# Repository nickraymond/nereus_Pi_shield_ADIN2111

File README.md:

# N6 Shield ADIN2111: in development, nothing designed yet

Branch `n6-shield`, started 2026-11-17. A shield for the back of the N6 board with Sofar's Bristlemouth mote
circuit, a 5 V supply and the motor driver, as small as possible.

**Read `BRIEF.md` first.** The project in `N6_Shield_ADIN2111/` is still an unchanged copy of the Pi Zero
side-entry shield (branch `pi-zero-side-entry`); it is the starting point, not an N6 design. Do not build it.

Docs, tools, references and the history of the Pi shields are on the `development` branch (`START_HERE.md`).

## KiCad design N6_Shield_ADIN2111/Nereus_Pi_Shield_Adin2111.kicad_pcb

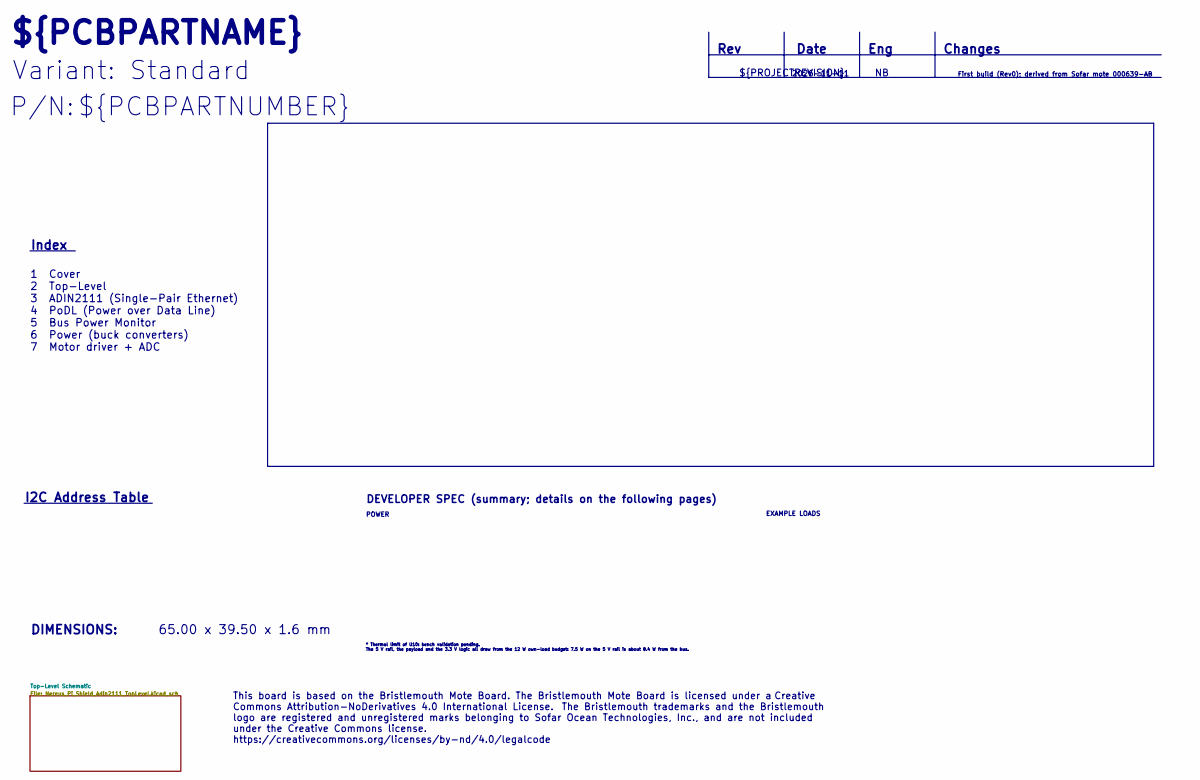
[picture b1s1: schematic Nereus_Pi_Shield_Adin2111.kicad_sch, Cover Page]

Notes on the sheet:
Variant: Standard
Date
${PCBPARTNAME}
Changes
${PCBPARTNUMBER}
First build (Rev0); derived from Sofar mote 000639-AB
Index
DEVELOPER SPEC (summary; details on the following pages)
2026-11-11
${PROJECTREVISION}
Rev
I2C Address Table
POWER
Eng
65.00 x 39.50 x 1.6 mm
1 Cover 2 Top-Level 3 ADIN2111 (Single-Pair Ethernet) 4 PoDL (Power over Data Line) 5 Bus Power Monitor 6 Power (buck converters) 7 Motor driver + ADC
* Thermal limit of U10: bench validation pending. The 5 V rail, the payload and the 3.3 V logic all draw from the 12 W own-load budget: 7.5 W on the 5 V rail is about 8.4 W from the bus.
P/N:
DIMENSIONS:
EXAMPLE LOADS
This board is based on the Bristlemouth Mote Board. The Bristlemouth Mote Board is licensed under a Creative Commons Attribution-NoDerivatives 4.0 International License. The Bristlemouth trademarks and the Bristlemouth logo are registered and unregistered marks belonging to Sofar Ocean Technologies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

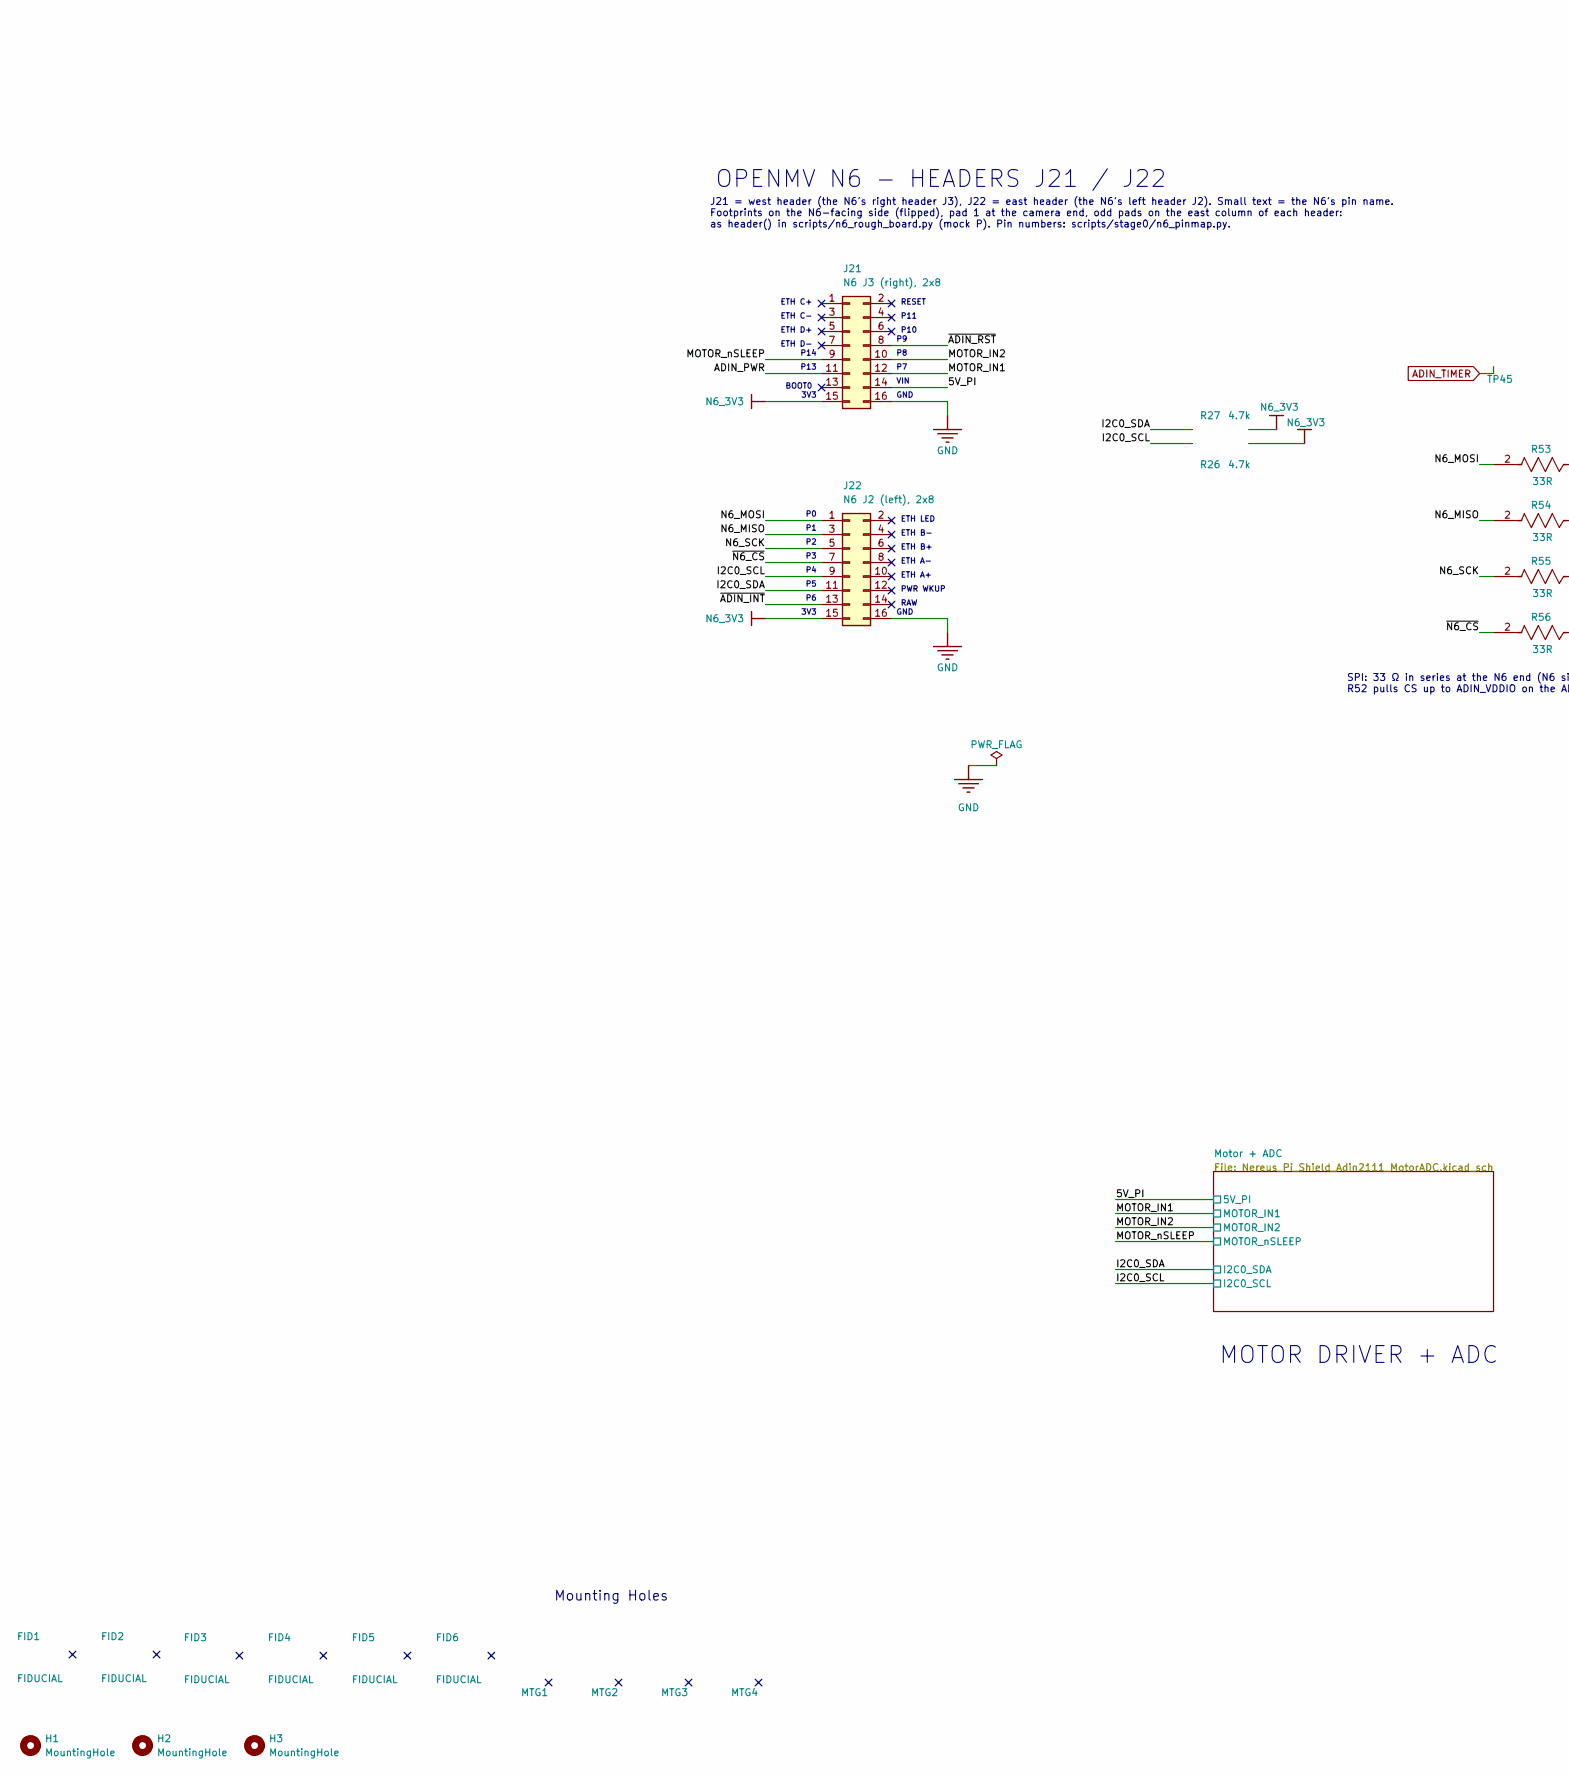
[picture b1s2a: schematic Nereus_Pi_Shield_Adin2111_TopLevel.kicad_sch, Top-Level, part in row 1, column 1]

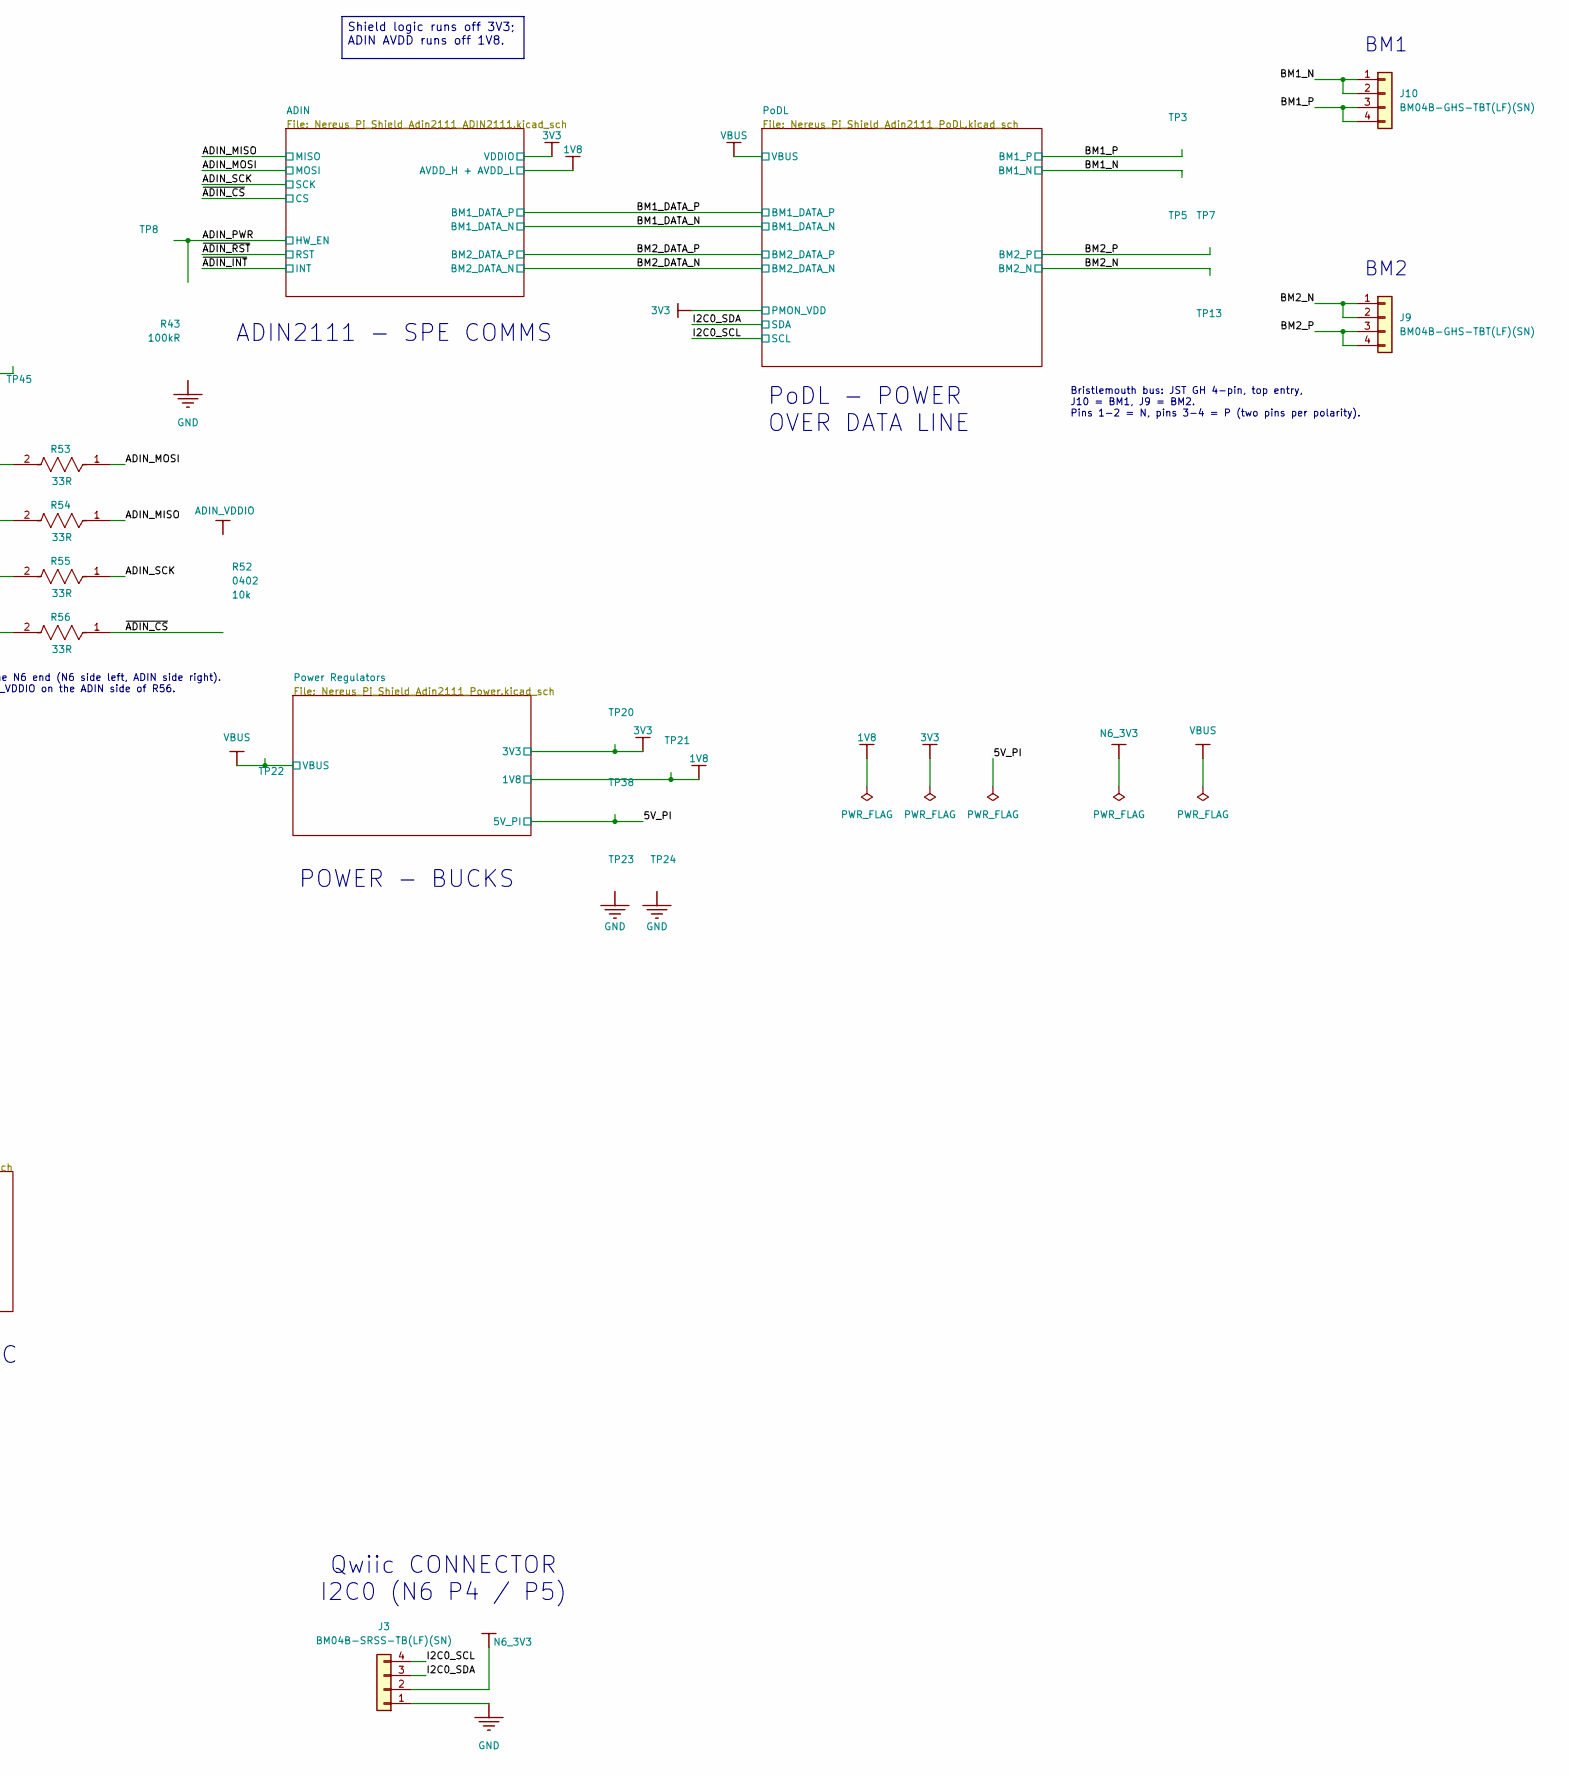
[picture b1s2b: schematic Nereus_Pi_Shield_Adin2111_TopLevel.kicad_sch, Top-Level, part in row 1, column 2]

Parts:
FID1, FID2, FID3, FID4, FID5, FID6: FIDUCIAL; FIDUCIAL_075MM
H1, H2, H3: MountingHole; MountingHole_2.7mm_M2.5_ISO7380
J3: BM04B-SRSS-TB(LF)(SN); JST_SH_BM04B-SRSS-TB_1x04-1MP_P1.00mm_Vertical
J9, J10: BM04B-GHS-TBT(LF)(SN); JST_GH_BM04B-GHS-TBT_1x04-1MP_P1.25mm_Vertical
J21: N6 J3 (right), 2x8; PinHeader_2x08_P2.54mm_Vertical
J22: N6 J2 (left), 2x8; PinHeader_2x08_P2.54mm_Vertical
MTG1, MTG2, MTG3, MTG4: Hole_M3
R26, R27: ERJ-2RKF4701X; RESC1005X40X25LL05T05; TOLERANCE 1%; VOLTAGE RATING 50 V; PARTNUMBER ERJ-2RKF4701X
R43: RMCF0402FT100K; FP-RMCF0402-IPC_C; TOLERANCE 1%; POWER RATING 62.5mW
R52: RC0402JR-0710KL; FP-RC0402-0_4-IPC_C; RESISTANCE TOLERANCE 5%; POWER RATING 62.5mW
R53, R54, R55, R56: 0402WGF330JTCE; FP-RC0402-0_4-IPC_B; WORKING VOLTAGE 50V; RESISTANCE TOLERANCE 1%
TP3, TP5, TP7, TP8, TP13, TP20, TP21, TP22, TP23, TP24, TP38, TP45: TEST_POINT; PCB_TP_1.5mm; PARTTYPE non BOM

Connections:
1V8: TP21.1 (1_1); also elsewhere on the board
3V3: TP20.1 (1_1); also elsewhere on the board
/Top-Level Schematic/5V_PI: J21.14, TP38.1 (1_1); also elsewhere on the board
/Top-Level Schematic/ADIN_MISO: R54.1; also elsewhere on the board
/Top-Level Schematic/ADIN_MOSI: R53.1; also elsewhere on the board
/Top-Level Schematic/ADIN_PWR: J21.11, R43.1, TP8.1 (1_1); also elsewhere on the board
/Top-Level Schematic/ADIN_SCK: R55.1; also elsewhere on the board
/Top-Level Schematic/BM1_N: J10.1, J10.2, TP5.1 (1_1); also elsewhere on the board
/Top-Level Schematic/BM1_P: J10.3, J10.4, TP3.1 (1_1); also elsewhere on the board
/Top-Level Schematic/BM2_N: J9.1, J9.2, TP13.1 (1_1); also elsewhere on the board
/Top-Level Schematic/BM2_P: J9.3, J9.4, TP7.1 (1_1); also elsewhere on the board
/Top-Level Schematic/I2C0_SCL: J3.4, J22.9, R26.1; also elsewhere on the board
/Top-Level Schematic/I2C0_SDA: J3.3, J22.11, R27.1; also elsewhere on the board
/Top-Level Schematic/MOTOR_IN1: J21.12; also elsewhere on the board
/Top-Level Schematic/MOTOR_IN2: J21.10; also elsewhere on the board
/Top-Level Schematic/MOTOR_nSLEEP: J21.9; also elsewhere on the board
/Top-Level Schematic/N6_MISO: J22.3, R54.2
/Top-Level Schematic/N6_MOSI: J22.1, R53.2
/Top-Level Schematic/N6_SCK: J22.5, R55.2
/Top-Level Schematic/~ADIN_CS: R52.2, R56.1; also elsewhere on the board
/Top-Level Schematic/~ADIN_INT: J22.13; also elsewhere on the board
/Top-Level Schematic/~ADIN_RST: J21.8; also elsewhere on the board
/Top-Level Schematic/~N6_CS: J22.7, R56.2
ADIN_TIMER: TP45.1 (1_1); also elsewhere on the board
ADIN_VDDIO: R52.1; also elsewhere on the board
GND: J3.1, J21.16, J22.16, R43.2, TP23.1 (1_1), TP24.1 (1_1); also elsewhere on the board
N6_3V3: J3.2, J21.15, J22.15, R26.2, R27.2; also elsewhere on the board
VBUS: TP22.1 (1_1); also elsewhere on the board

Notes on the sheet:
ETH C-
RAW
J21 = west header (the N6's right header J3), J22 = east header (the N6's left header J2). Small text = the N6's pin name. Footprints on the N6-facing side (flipped), pad 1 at the camera end, odd pads on the east column of each header: as header() in scripts/n6_rough_board.py (mock P). Pin numbers: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
P11
GND
RESET
ETH LED
ETH B+
3V3
P13
BM1
PWR WKUP
VIN
ETH B-
BM2
Bristlemouth bus: JST GH 4-pin, top entry, J10 = BM1, J9 = BM2. Pins 1-2 = N, pins 3-4 = P (two pins per polarity).
ETH D-
ETH D+
P14
BOOT0
ETH C+
SPI: 33 Ω in series at the N6 end (N6 side left, ADIN side right). R52 pulls CS up to ADIN_VDDIO on the ADIN side of R56.
ETH A+
ETH A-
P10
Shield logic runs off 3V3; ADIN AVDD runs off 1V8.
MOTOR DRIVER + ADC
Qwiic CONNECTOR I2C0 (N6 P4 / P5)
OPENMV N6 - HEADERS J21 / J22
PoDL - POWER OVER DATA LINE
ADIN2111 - SPE COMMS
Mounting Holes
POWER - BUCKS

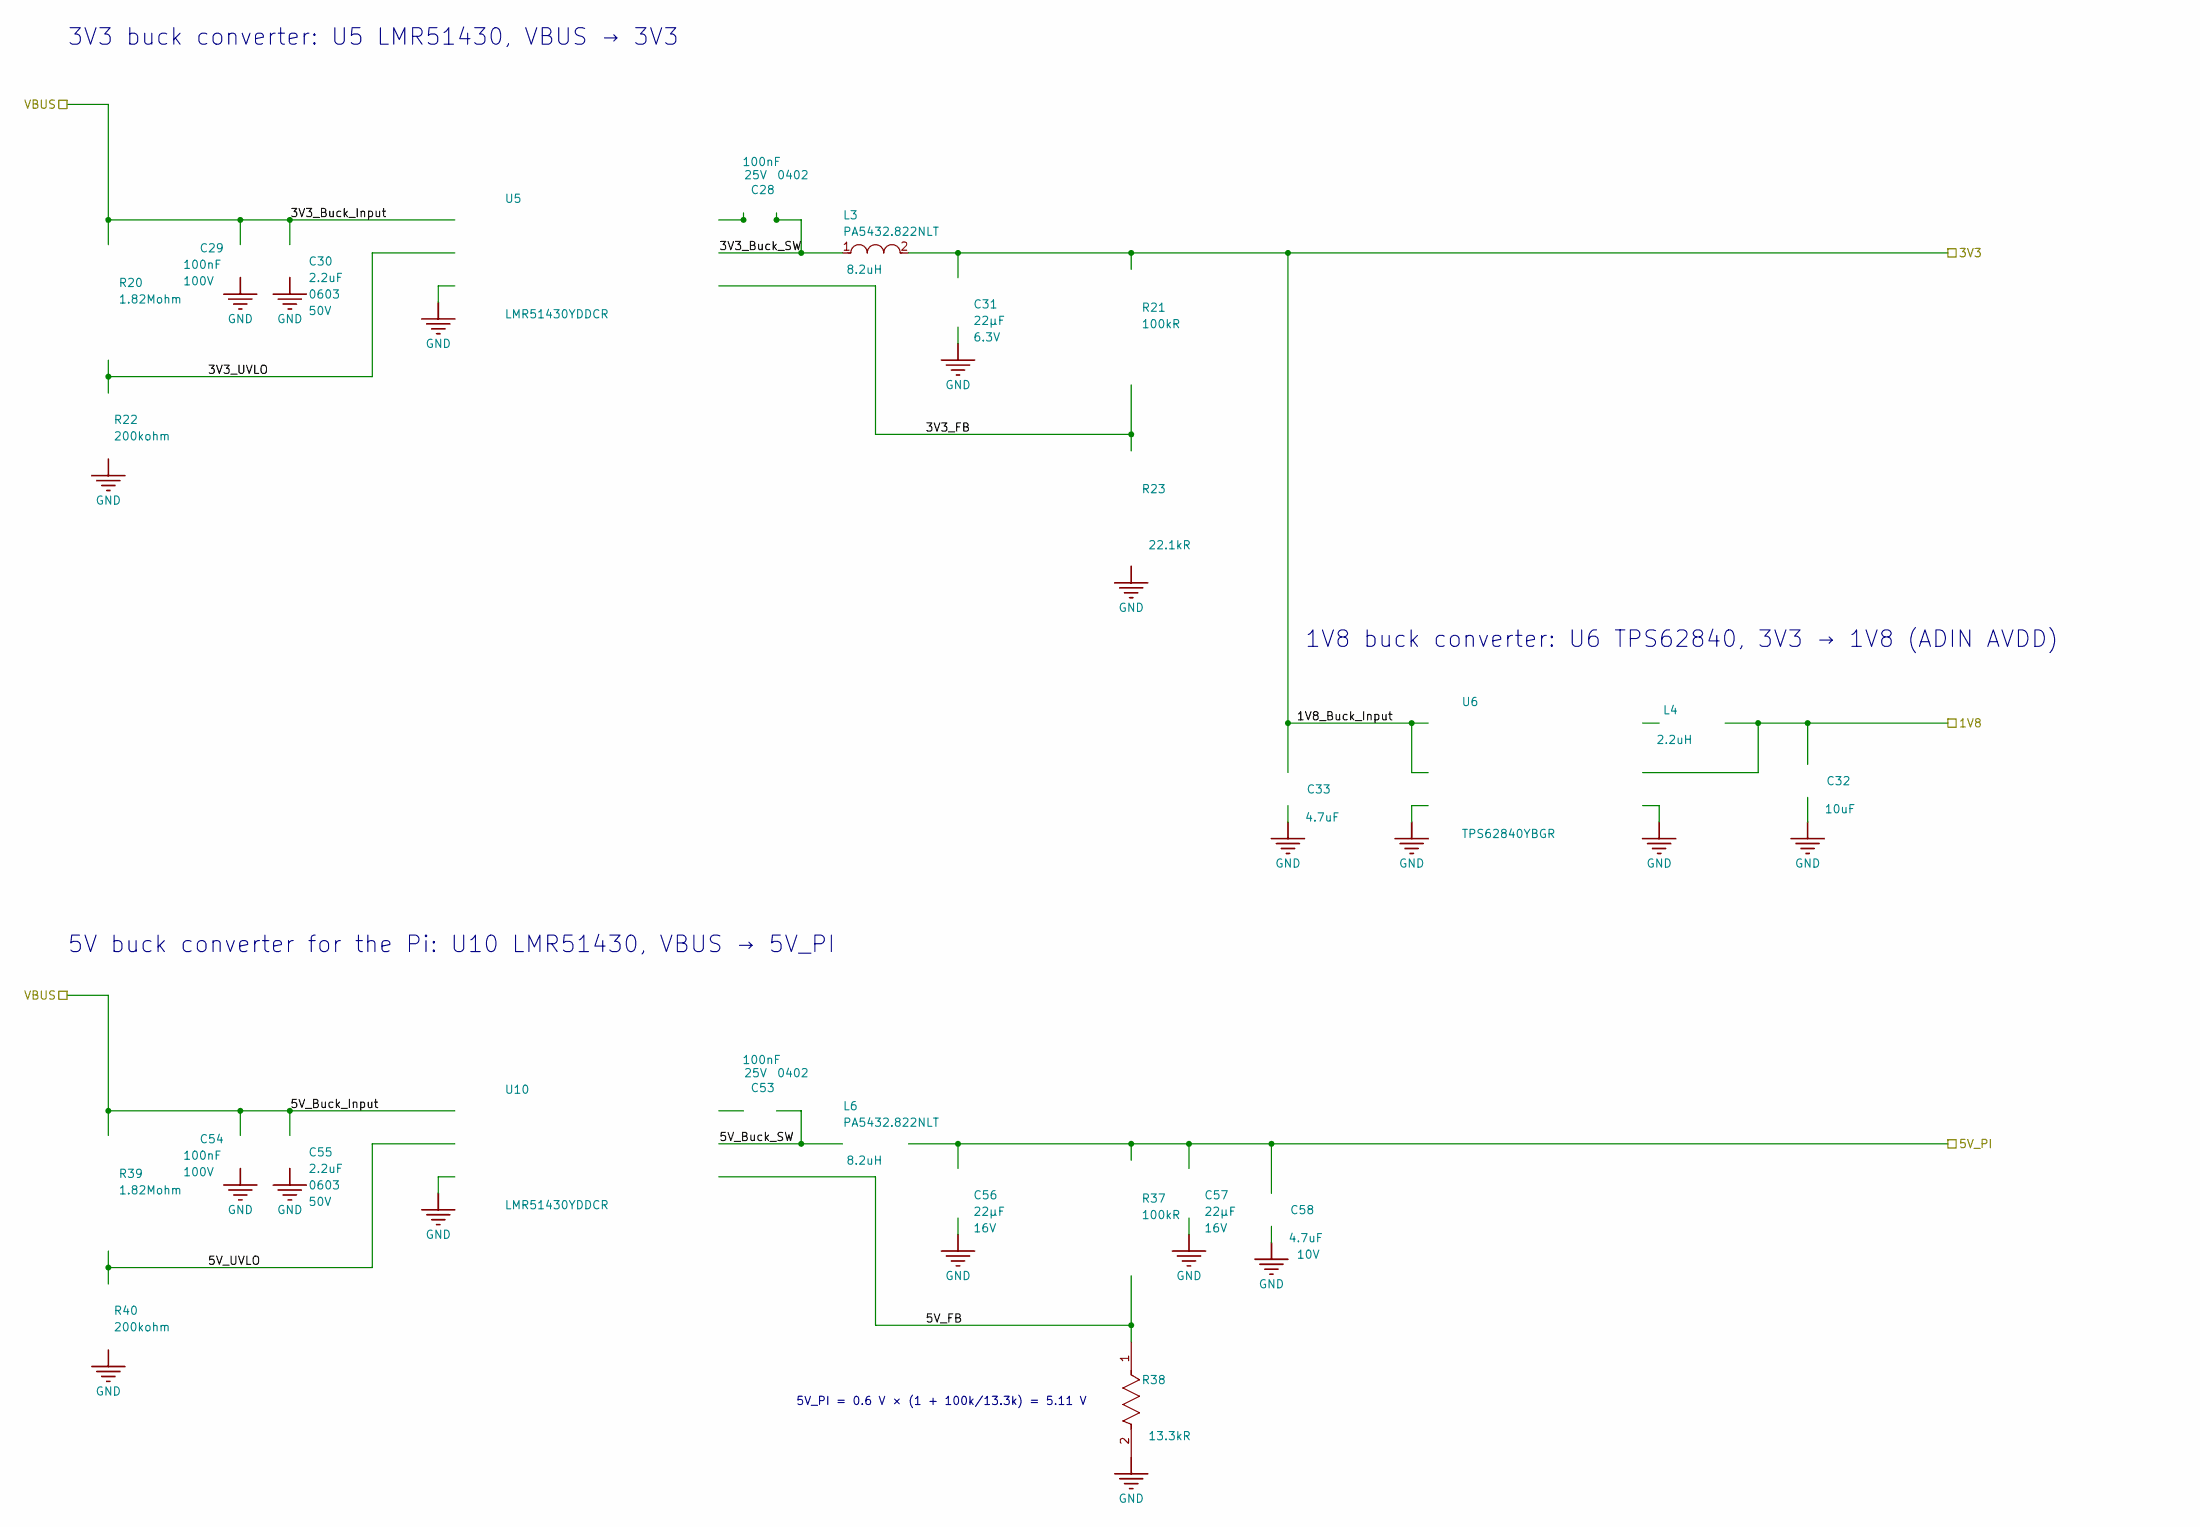
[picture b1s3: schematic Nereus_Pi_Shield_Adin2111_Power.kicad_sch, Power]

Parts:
C28, C53: CL05A104KA5NNNC; FP-CL278-IPC_C; VOLTAGE 25V; VOLTAGE RATING 25V
C29, C54: GRM188R72A104KA35D; FP-GRM188-0_1-e0_2_0_5-IPC_B; VOLTAGE RATING (DC) 100V; VOLTAGE 100V
C30, C55: UMK107BBJ225KA-T; FP-0603-L_1_6_0_2-W_0_8_0-MFG; VOLTAGE RATING 50V; TOLERANCE 10%
C31: C1608X5R0J226M080AC; CAPC1608X100X20ML10; TOLERANCE ±20%; VOLTAGE - RATED 6.3V
C32: GRJ155R60J106ME11D; FP-GRJ155-0_2-MFG; TOLERANCE 20%; VOLTAGE RATING 6.3V
C33: GRM155R60J475ME87D; FP-GRM155-0_15-MFG; TOLERANCE 20%; VOLTAGE 6.3V
C56, C57: GRM21BR61C226ME44L; C_0805_2012Metric; TOLERANCE ±20%; VOLTAGE - RATED 16V
C58: GRM155R61A475MEAAD; C_0402_1005Metric; TOLERANCE 20%; VOLTAGE RATING 10V
L3, L6: PA5432.822NLT; FP-PA5432_472NLT-MFG
L4: DFE201612E-2R2M=P2; FP-DFE201612C-MFG
R20, R39: CRCW04021M82FKED; FP-CRCW0402-e3-MFG; RESISTANCE TOLERANCE 1%; POWER RATING 63mW
R21, R37: RMCF0402FT100K; FP-RMCF0402-IPC_C; TOLERANCE 1%; POWER RATING 62.5mW
R22, R40: RC0402FR-07200KL; RESC1005X40X25LL05T10; PART NUMBER RC0402FR-07200KL
R23: RC0402FR-0722K1L; FP-RC0402-0_4-IPC_B; WORKING VOLTAGE 50V; RESISTANCE TOLERANCE 1%
R38: 0402WGF1332TCE; FP-RC0402-0_4-IPC_B; WORKING VOLTAGE 50V; RESISTANCE TOLERANCE 1%
U5, U10: LMR51430YDDCR; SOT-23-THIN-6_DDC_TEX; MANUFACTURER_PART_NUMBER LMR51430YDDCR
U6: TPS62840YBGR; FP-YBG0006-MFG

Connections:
1V8: C32.1, L4.2, U6.A2 (VOS); also elsewhere on the board
3V3: C31.2, C33.1, L3.2, R21.1, U6.B1 (VIN), U6.C1 (EN); also elsewhere on the board
/Top-Level Schematic/5V_PI: C56.2, C57.2, C58.1, L6.2, R37.1; also elsewhere on the board
/Top-Level Schematic/Power Regulators/3V3_Buck_SW: C28.1, L3.1, U5.2 (SW)
/Top-Level Schematic/Power Regulators/3V3_FB: R21.2, R23.1, U5.4 (FB)
/Top-Level Schematic/Power Regulators/3V3_UVLO: R20.1, R22.2, U5.5 (EN)
/Top-Level Schematic/Power Regulators/5V_Buck_SW: C53.1, L6.1, U10.2 (SW)
/Top-Level Schematic/Power Regulators/5V_FB: R37.2, R38.1, U10.4 (FB)
/Top-Level Schematic/Power Regulators/5V_UVLO: R39.1, R40.2, U10.5 (EN)
GND: C29.2, C30.2, C31.1, C32.2, C33.2, C54.2, C55.2, C56.1, C57.1, C58.2, R22.1, R23.2, R38.2, R40.1, U5.1 (GND), U6.A1 (GND), U6.C2 (VSET), U10.1 (GND); also elsewhere on the board
unnamed: C28.2, U5.6 (CB)
unnamed: L4.1, U6.B2 (SW)
unnamed: C53.2, U10.6 (CB)
VBUS: C29.1, C30.1, C54.1, C55.1, R20.2, R39.2, U5.3 (VIN), U10.3 (VIN); also elsewhere on the board

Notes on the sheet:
1V8 buck converter: U6 TPS62840, 3V3 → 1V8 (ADIN AVDD)
3V3 buck converter: U5 LMR51430, VBUS → 3V3
5V buck converter for the Pi: U10 LMR51430, VBUS → 5V_PI
5V_PI = 0.6 V × (1 + 100k/13.3k) = 5.11 V

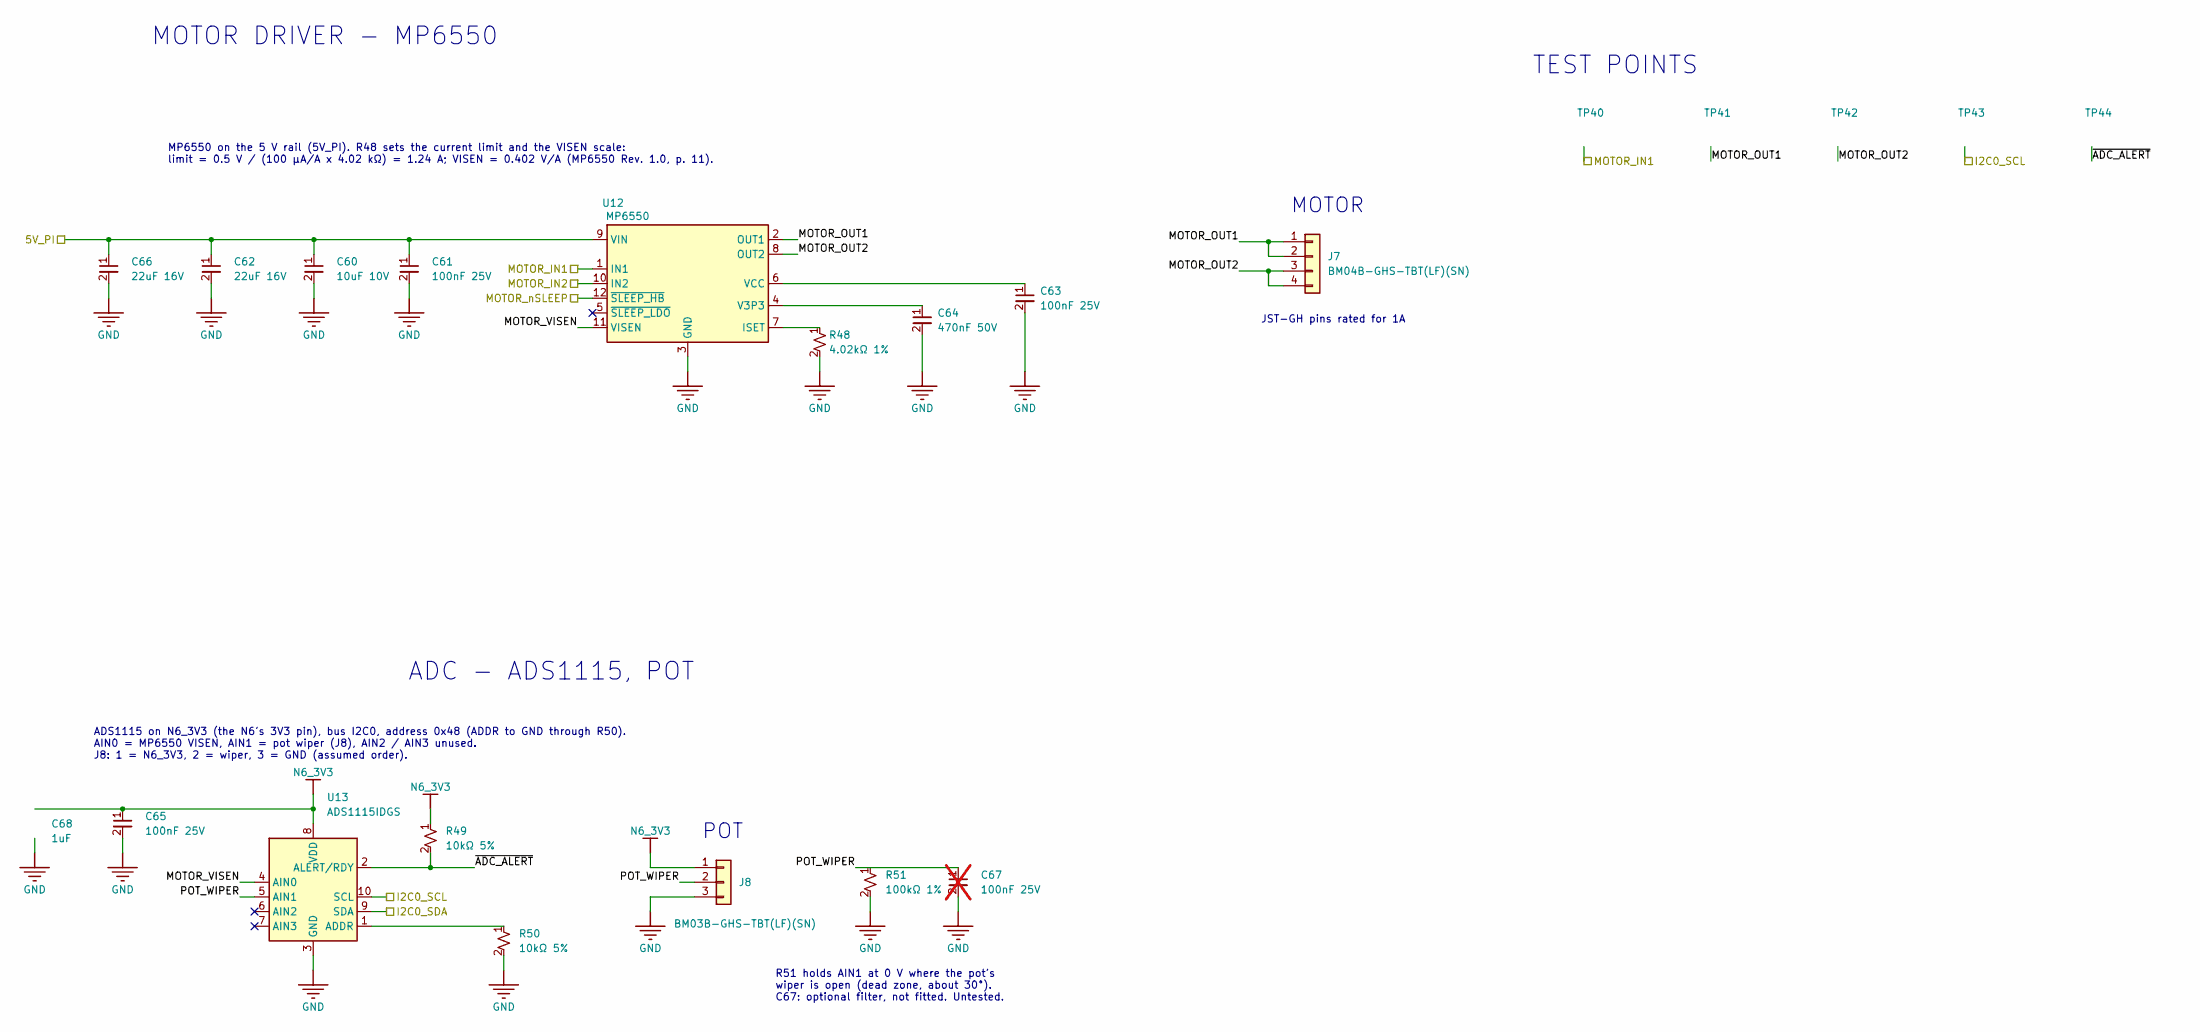
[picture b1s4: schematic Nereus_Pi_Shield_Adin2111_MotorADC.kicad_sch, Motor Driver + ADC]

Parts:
C60: 10uF 10V; C_0402_1005Metric_Pad0.74x0.62mm_HandSolder
C61, C63, C65: 100nF 25V; FP-CL278-IPC_C
C62, C66: 22uF 16V; C_0805_2012Metric
C64: 470nF 50V; C_0402_1005Metric_Pad0.74x0.62mm_HandSolder
C67: 100nF 25V; FP-CL278-IPC_C; not fitted
C68: CL05A105KP5NNNC; FP-CL511-IPC_C; TOLERANCE 10%; VOLTAGE RATING 10V
J7: BM04B-GHS-TBT(LF)(SN); JST_GH_BM04B-GHS-TBT_1x04-1MP_P1.25mm_Vertical
J8: BM03B-GHS-TBT(LF)(SN); JST_GH_BM03B-GHS-TBT_1x03-1MP_P1.25mm_Vertical
R48: 4.02kΩ 1%; FP-RC0402-0_4-IPC_C
R49, R50: 10kΩ 5%; FP-RC0402-0_4-IPC_C
R51: 100kΩ 1%; FP-RMCF0402-IPC_C
TP40, TP41, TP42, TP43, TP44: TEST_POINT; PCB_TP_1.5mm; PARTTYPE non BOM
U12: MP6550; MP6550GG
U13: ADS1115IDGS; TSSOP-10_3x3mm_P0.5mm

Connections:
/Top-Level Schematic/5V_PI: C60.1, C61.1, C62.1, C66.1, U12.9 (VIN); also elsewhere on the board
/Top-Level Schematic/I2C0_SCL: TP43.1 (1_1), U13.10 (SCL); also elsewhere on the board
/Top-Level Schematic/I2C0_SDA: U13.9 (SDA); also elsewhere on the board
/Top-Level Schematic/MOTOR_IN1: TP40.1 (1_1), U12.1 (IN1); also elsewhere on the board
/Top-Level Schematic/MOTOR_IN2: U12.10 (IN2); also elsewhere on the board
/Top-Level Schematic/MOTOR_nSLEEP: U12.12 (~SLEEP_HB); also elsewhere on the board
/Top-Level Schematic/Motor + ADC/MOTOR_OUT1: J7.1, J7.2, TP41.1 (1_1), U12.2 (OUT1)
/Top-Level Schematic/Motor + ADC/MOTOR_OUT2: J7.3, J7.4, TP42.1 (1_1), U12.8 (OUT2)
/Top-Level Schematic/Motor + ADC/MOTOR_VISEN: U12.11 (VISEN), U13.4 (AIN0)
/Top-Level Schematic/Motor + ADC/POT_WIPER: C67.1, J8.2, R51.1, U13.5 (AIN1)
/Top-Level Schematic/Motor + ADC/~ADC_ALERT: R49.2, TP44.1 (1_1), U13.2 (ALERT/RDY)
GND: C60.2, C61.2, C62.2, C63.2, C64.2, C65.2, C66.2, C67.2, C68.2, J8.3, R48.2, R50.2, R51.2, U12.3 (GND), U13.3 (GND); also elsewhere on the board
N6_3V3: C65.1, C68.1, J8.1, R49.1, U13.8 (VDD); also elsewhere on the board
unnamed: R48.1, U12.7 (ISET)
unnamed: C64.1, U12.4 (V3P3)
unnamed: C63.1, U12.6 (VCC)
unnamed: R50.1, U13.1 (ADDR)

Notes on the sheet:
MP6550 on the 5 V rail (5V_PI). R48 sets the current limit and the VISEN scale: limit = 0.5 V / (100 µA/A x 4.02 kΩ) = 1.24 A; VISEN = 0.402 V/A (MP6550 Rev. 1.0, p. 11).
ADS1115 on N6_3V3 (the N6's 3V3 pin), bus I2C0, address 0x48 (ADDR to GND through R50). AIN0 = MP6550 VISEN, AIN1 = pot wiper (J8), AIN2 / AIN3 unused. J8: 1 = N6_3V3, 2 = wiper, 3 = GND (assumed order).
JST-GH pins rated for 1A
POT
MOTOR
R51 holds AIN1 at 0 V where the pot's wiper is open (dead zone, about 30°). C67: optional filter, not fitted. Untested.
ADC - ADS1115, POT
MOTOR DRIVER - MP6550
TEST POINTS

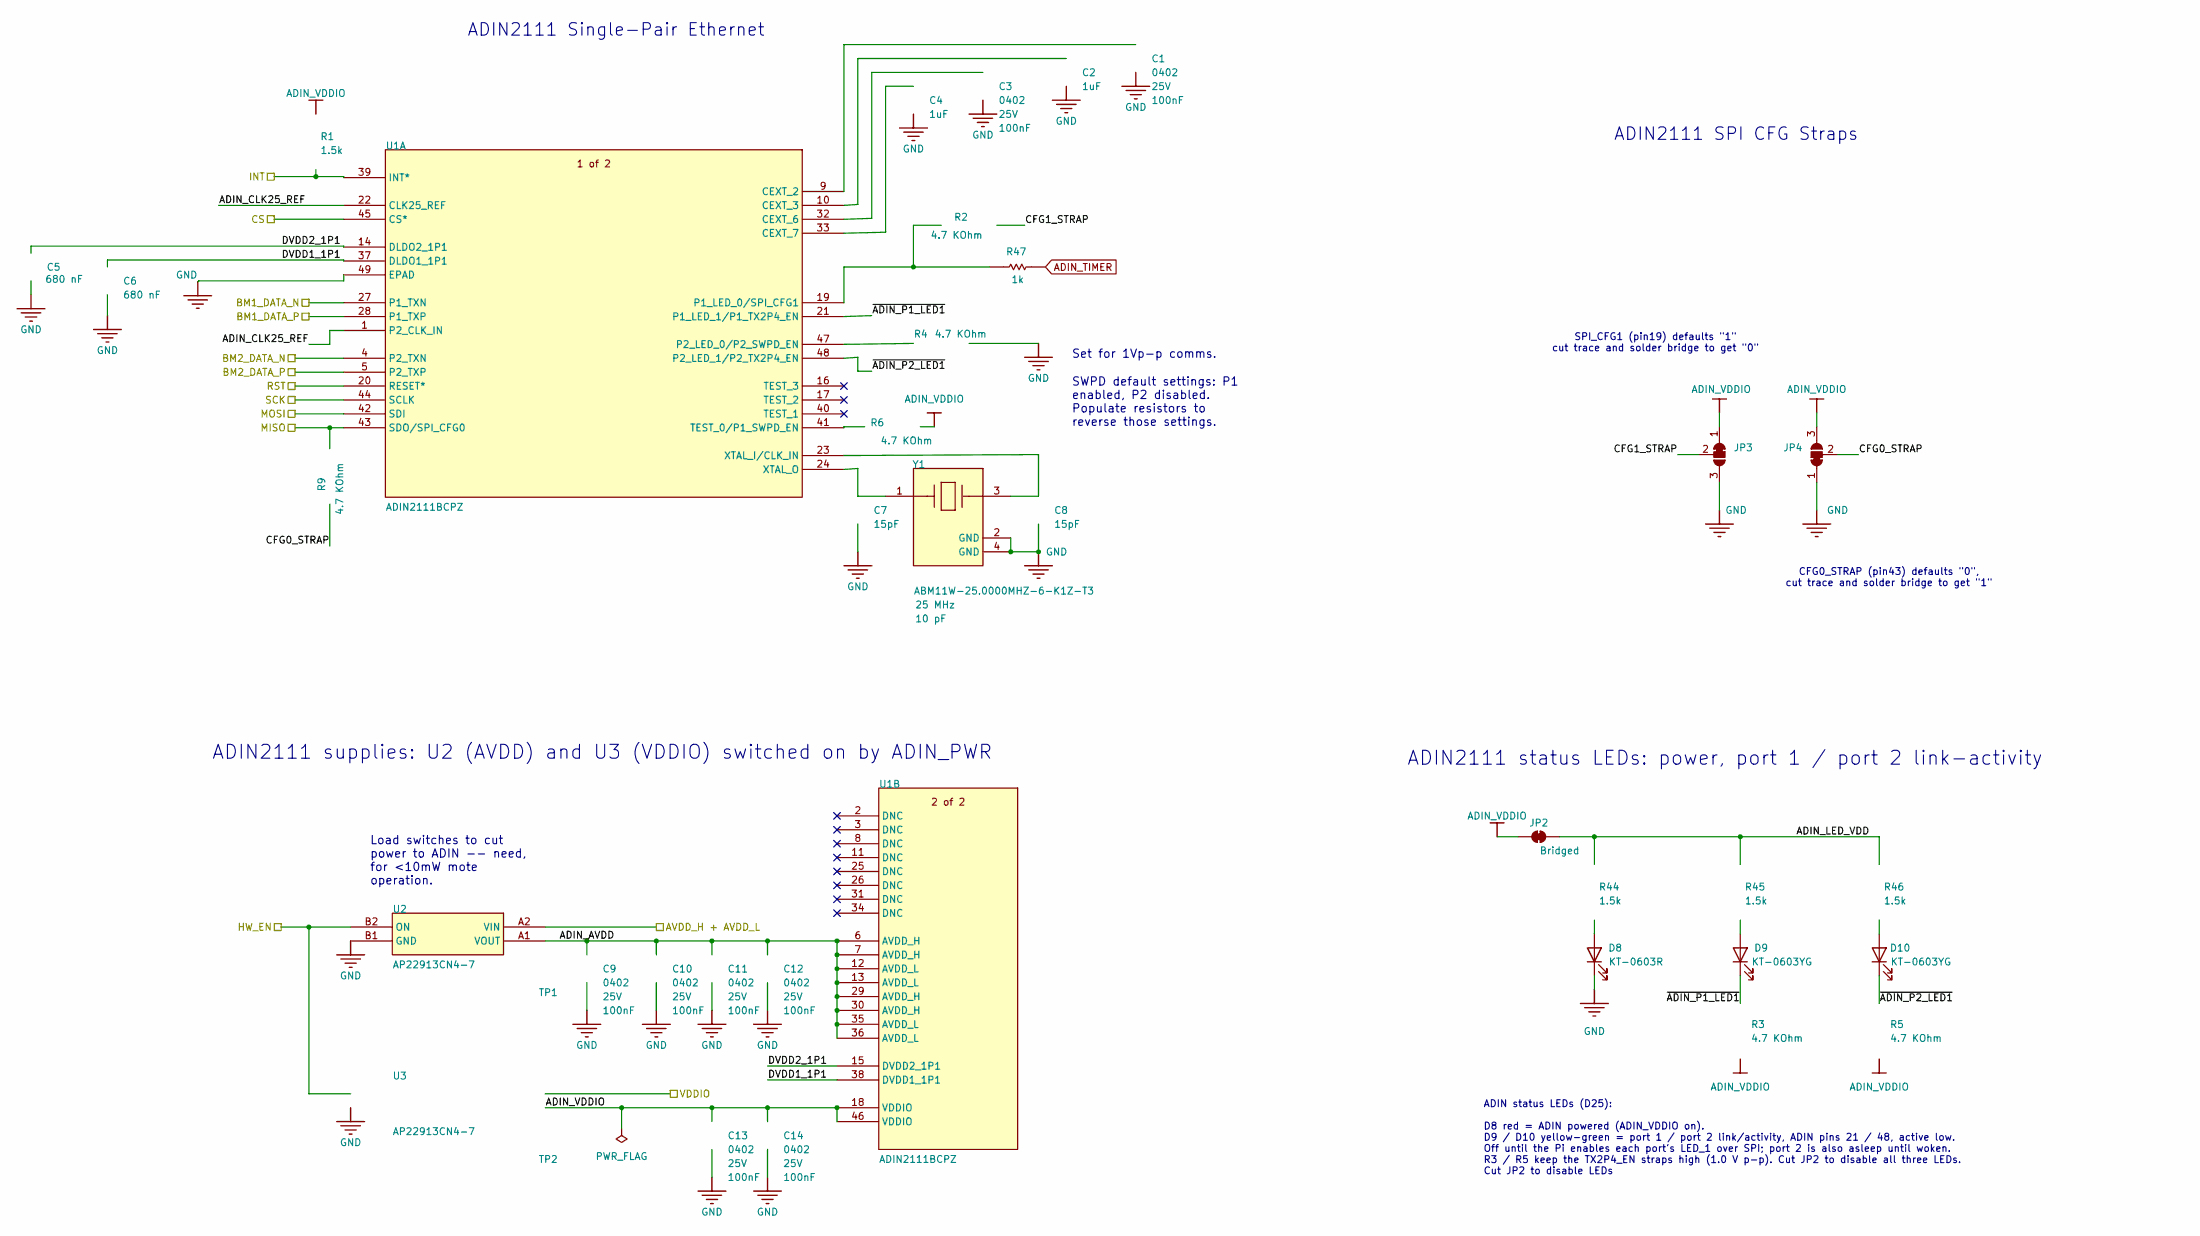
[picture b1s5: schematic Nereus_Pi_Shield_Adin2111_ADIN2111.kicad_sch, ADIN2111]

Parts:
C1, C3, C9, C10, C11, C12, C13, C14: CL05A104KA5NNNC; FP-CL278-IPC_C; VOLTAGE 25V; VOLTAGE RATING 25V
C2, C4: CL05A105KP5NNNC; FP-CL511-IPC_C; TOLERANCE 10%; VOLTAGE RATING 10V
C5, C6: CC0402KRX5R6BB684; FP-CC0402-MFG; TOLERANCE 0.1; VOLTAGE RATING 10 V; MANUFACTURER PART NUMBER CC0402KRX5R6BB684; DIGIKEY DESCRIPTION CAP CER 0.68UF 10V X5R 0402
C7, C8: CC0402JRNPO9BN150; FP-CC0402-0_55-IPC_B; VOLTAGE RATING (DC) 50V; VOLTAGE RATING 50V
D8: KT-0603R; LED_0603_1608Metric; LCSC C2286
D9, D10: KT-0603YG; LED_0603_1608Metric; LCSC C2289
JP2: Bridged; SolderJumper-2_R1210_Bridged_NetTie
JP3, JP4: SolderJumper_3_Bridged12; SolderJumper-3_P1.3mm_Bridged12_RoundedPad1.0x1.5mm
R1, R44, R45, R46: RC0402FR-071K5L; RESC1005X40X25ML05T10; PART NUMBER RC0402FR-071K5L
R2, R3, R4, R5, R6, R9: ERJ-2RKF4701X; RESC1005X40X25LL05T05; TOLERANCE 1%; VOLTAGE RATING 50 V; PARTNUMBER ERJ-2RKF4701X
R47: RC0402FR-071KL; RESC1005X40X25ML05T10; PART NUMBER RC0402FR-071KL
TP1, TP2: TEST_POINT; PCB_TP_1.5mm; PARTTYPE non BOM
U1: ADIN2111BCPZ; ADIN2111BCPZ-Footprint-1
U2, U3: AP22913CN4-7; AP22913CN4-7-Footprint-1
Y1: ABM11W-25.0000MHZ-6-K1Z-T3; FP-ABM11W-MFG

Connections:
1V8: U2.A2 (VIN); also elsewhere on the board
3V3: U3.A2 (VIN); also elsewhere on the board
/Top-Level Schematic/ADIN/ADIN_AVDD: C9.1, C10.1, C11.1, C12.1, TP1.1 (1_1), U1.6 (AVDD_H), U1.7 (AVDD_H), U1.12 (AVDD_L), U1.13 (AVDD_L), U1.29 (AVDD_H), U1.30 (AVDD_H), U1.35 (AVDD_L), U1.36 (AVDD_L), U2.A1 (VOUT)
/Top-Level Schematic/ADIN/ADIN_CLK25_REF: U1.1 (P2_CLK_IN), U1.22 (CLK25_REF)
/Top-Level Schematic/ADIN/ADIN_LED_VDD: JP2.2 (B), R44.2, R45.2, R46.2
/Top-Level Schematic/ADIN/CFG0_STRAP: JP4.2 (C), R9.1
/Top-Level Schematic/ADIN/CFG1_STRAP: JP3.2 (C), R2.2
/Top-Level Schematic/ADIN/DVDD1_1P1: C6.1, U1.37 (DLDO1_1P1), U1.38 (DVDD1_1P1)
/Top-Level Schematic/ADIN/DVDD2_1P1: C5.1, U1.14 (DLDO2_1P1), U1.15 (DVDD2_1P1)
/Top-Level Schematic/ADIN/~ADIN_P1_LED1: D9.1 (K), R3.1, U1.21 (P1_LED_1/P1_TX2P4_EN)
/Top-Level Schematic/ADIN/~ADIN_P2_LED1: D10.1 (K), R5.1, U1.48 (P2_LED_1/P2_TX2P4_EN)
/Top-Level Schematic/ADIN_MISO: R9.2, U1.43 (SDO/SPI_CFG0); also elsewhere on the board
/Top-Level Schematic/ADIN_MOSI: U1.42 (SDI); also elsewhere on the board
/Top-Level Schematic/ADIN_PWR: U2.B2 (ON), U3.B2 (ON); also elsewhere on the board
/Top-Level Schematic/ADIN_SCK: U1.44 (SCLK); also elsewhere on the board
/Top-Level Schematic/BM1_DATA_N: U1.27 (P1_TXN); also elsewhere on the board
/Top-Level Schematic/BM1_DATA_P: U1.28 (P1_TXP); also elsewhere on the board
/Top-Level Schematic/BM2_DATA_N: U1.4 (P2_TXN); also elsewhere on the board
/Top-Level Schematic/BM2_DATA_P: U1.5 (P2_TXP); also elsewhere on the board
/Top-Level Schematic/~ADIN_CS: U1.45 (CS*); also elsewhere on the board
/Top-Level Schematic/~ADIN_INT: R1.1, U1.39 (INT*); also elsewhere on the board
/Top-Level Schematic/~ADIN_RST: U1.20 (RESET*); also elsewhere on the board
ADIN_TIMER: R47.1; also elsewhere on the board
ADIN_VDDIO: C13.1, C14.1, JP2.1 (A), JP3.1 (A), JP4.3 (B), R1.2, R3.2, R5.2, R6.2, TP2.1 (1_1), U1.18 (VDDIO), U1.46 (VDDIO), U3.A1 (VOUT); also elsewhere on the board
GND: C1.2, C2.2, C3.2, C4.2, C5.2, C6.2, C7.2, C8.2, C9.2, C10.2, C11.2, C12.2, C13.2, C14.2, D8.1 (K), JP3.3 (B), JP4.1 (A), R4.2, U1.49 (EPAD), U2.B1 (GND), U3.B1 (GND), Y1.2 (GND), Y1.4 (GND); also elsewhere on the board
unnamed: D8.2 (A), R44.1
unnamed: D9.2 (A), R45.1
unnamed: D10.2 (A), R46.1
unnamed: C1.1, U1.9 (CEXT_2)
unnamed: C2.1, U1.10 (CEXT_3)
unnamed: C3.1, U1.32 (CEXT_6)
unnamed: C4.1, U1.33 (CEXT_7)
unnamed: R2.1, R47.2, U1.19 (P1_LED_0/SPI_CFG1)
unnamed: R4.1, U1.47 (P2_LED_0/P2_SWPD_EN)
unnamed: R6.1, U1.41 (TEST_0/P1_SWPD_EN)
unnamed: C8.1, U1.23 (XTAL_I/CLK_IN), Y1.3
unnamed: C7.1, U1.24 (XTAL_O), Y1.1

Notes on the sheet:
ADIN2111 status LEDs: power, port 1 / port 2 link-activity
ADIN2111 supplies: U2 (AVDD) and U3 (VDDIO) switched on by ADIN_PWR
CFG0_STRAP (pin43) defaults "0", cut trace and solder bridge to get "1"
ADIN status LEDs (D25): D8 red = ADIN powered (ADIN_VDDIO on). D9 / D10 yellow-green = port 1 / port 2 link/activity, ADIN pins 21 / 48, active low. Off until the Pi enables each port's LED_1 over SPI; port 2 is also asleep until woken. R3 / R5 keep the TX2P4_EN straps high (1.0 V p-p). Cut JP2 to 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
SPI_CFG1 (pin19) defaults "1" cut trace and solder bridge to get "0"
Set for 1Vp-p comms.
Load switches to cut power to ADIN -- need, for <10mW mote operation.
ADIN2111 SPI CFG Straps
ADIN2111 Single-Pair Ethernet
SWPD default settings: P1 enabled, P2 disabled. Populate resistors to reverse those settings.

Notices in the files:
N6_Shield_ADIN2111/Nereus_Pi_Shield_Adin2111.kicad_sch:
The Bristlemouth Mote Board is licensed under a Creative Commons Attribution-NoDerivatives 4.0 International License.  The Bristlemouth trademarks and the Bristlemouth logo are registered and unregistered marks belonging to Sofar Ocean Technologies, Inc., and are not included under the Creative Com
https://creativecommons.org/licenses/by-nd/4.0/legalcode
